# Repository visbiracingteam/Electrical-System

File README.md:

# Overview
### Contains all the files related to Electrical System of IITB-Racing

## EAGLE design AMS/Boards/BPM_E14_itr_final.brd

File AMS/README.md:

# AMS
### Contains all the files related to Accumulator Management System

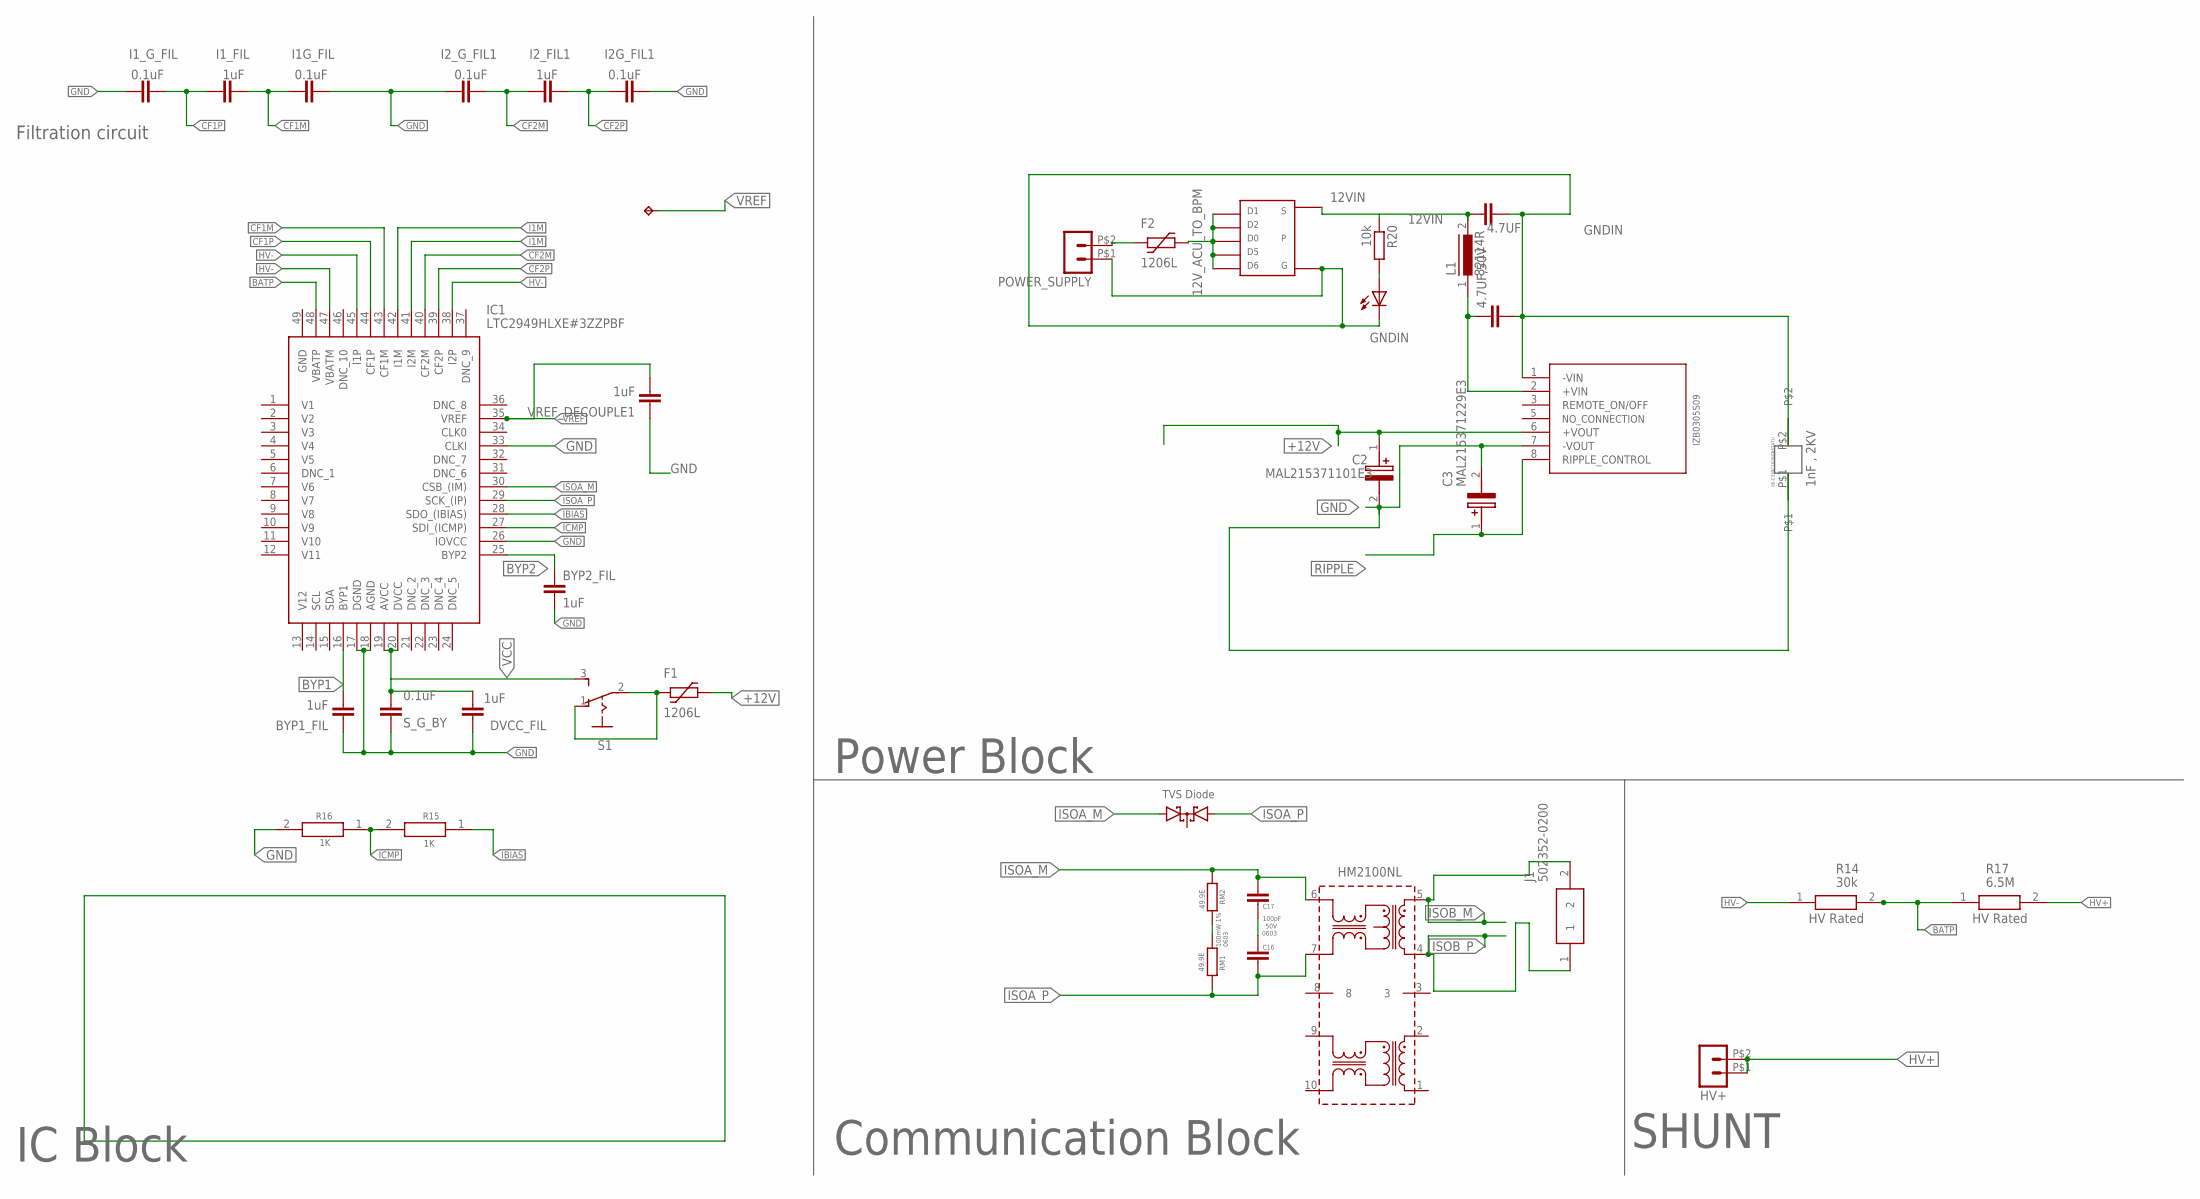
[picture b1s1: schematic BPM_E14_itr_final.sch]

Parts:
4.7UF, 4.7UF,50V: C-EUC1206; C1206
BYP1_FIL, BYP2_FIL: 1uF; C0603
C2: MAL215371101E3; CAPAE1060X1060N
C3: MAL215371229E3; CAPAE860X680N
C15: TPPAD1-13; P1-13
C16, C17: 100pF; C0603
DVCC_FIL: 1uF; C0603
F1, F2: 1206L
HM2100NL: HM2100NL
HV+: MOLEX2PIN43650-0200; 43650-0200
I1G_FIL, I1_G_FIL, I2G_FIL1, I2_G_FIL1: 0.1uF; C0603
I1_FIL, I2_FIL1: 1uF; C0603
IC1: LTC2949HLXE#3ZZPBF; QFP50P900X900X160-49N
IM1: TVS; SOT23
J1: 502352-0200; 5023520200
L1: 82114R
POWER_SUPPLY: MOLEX2PIN43045-0212; 43045-0212
PWR_LED: LED-FKIT-1206; FKIT-LED-1206
R14: 30k; RESC3216X70N
R15, R16: 1K; RESC1608X50N
R17: 6.5M; RESC3216X70N
R20: 10k; R0805
RM1, RM2: 49.9E; R0603
S1: STS121PC04
S_G_BY: 0.1uF; C0603
U$1: BPM_CONV
U$2: 80-C330C102KGR5TATU
U$10: TSOP-6_PMOS
VREF_DECOUPLE1: 1uF; C0603

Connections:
12VIN: 4.7UF.1, L1.2, R20.1, U$10.S
12V_ACU_TO_BPM: F2.P$2 (2), U$10.1, U$10.2, U$10.5, U$10.6, U$10.D (D0)
+12V: C2.1 (+), F1.P$2 (2), U$1.6 (+VOUT)
BATP: IC1.48 (VBATP), R14.2, R17.1
BYP1: BYP1_FIL.2, IC1.16 (BYP1)
BYP2: BYP2_FIL.1, IC1.25 (BYP2)
CF1M: I1G_FIL.1, I1_FIL.1, IC1.43 (CF1M)
CF1P: I1_FIL.2, I1_G_FIL.2, IC1.44 (CF1P)
CF2M: I2_FIL1.2, I2_G_FIL1.1, IC1.40 (CF2M)
CF2P: I2G_FIL1.1, I2_FIL1.1, IC1.39 (CF2P)
GND: BYP1_FIL.1, BYP2_FIL.2, C2.2 (-), C3.2 (-), DVCC_FIL.1, I1G_FIL.2, I1_G_FIL.1, I2G_FIL1.2, I2_G_FIL1.2, IC1.17 (DGND), IC1.18 (AGND), IC1.26 (IOVCC), IC1.33 (CLKI), R16.2, S_G_BY.1, U$1.7 (-VOUT), U$2.P$1, VREF_DECOUPLE1.1
GNDIN: 4.7UF.2, 4.7UF,50V.2, POWER_SUPPLY.P$1 (1), PWR_LED.C, U$1.1 (-VIN), U$2.P$2, U$10.G
HV+: HV+.P$1 (1), HV+.P$2 (2), R17.2
HV-: IC1.38 (I2P), IC1.45 (I1P), IC1.47 (VBATM), R14.1
I1M: IC1.41 (I2M), IC1.42 (I1M)
IBIAS: IC1.28 (SDO_(IBIAS)), R15.1
ICMP: IC1.27 (SDI_(ICMP)), R15.2, R16.1
ISOA_M: C17.2, HM2100NL.6, IC1.30 (CSB_(IM)), IM1.2 (A2), RM2.1
ISOA_P: C16.1, HM2100NL.7, IC1.29 (SCK_(IP)), IM1.1 (A1), RM1.2
ISOB_M: HM2100NL.5, J1.2
ISOB_P: HM2100NL.4, J1.1
N$: RM1.1, RM2.2
unnamed: 4.7UF,50V.1, L1.1, U$1.2 (+VIN)
unnamed: F2.P$1 (1), POWER_SUPPLY.P$2 (2)
unnamed: PWR_LED.A, R20.2
unnamed: F1.P$1 (1), S1.1 (O), S1.2
unnamed: C16.2, C17.1
RIPPLE: C3.1 (+), U$1.8 (RIPPLE_CONTROL)
VCC: DVCC_FIL.2, IC1.19 (AVCC), IC1.20 (DVCC), S1.3 (S), S_G_BY.2
VREF: C15.TP, IC1.35 (VREF), VREF_DECOUPLE1.2

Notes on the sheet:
50V 0603
100mW 1% 0603
TVS Diode
Communication Block
IC Block
SHUNT
Power Block
Filtration circuit
HV Rated

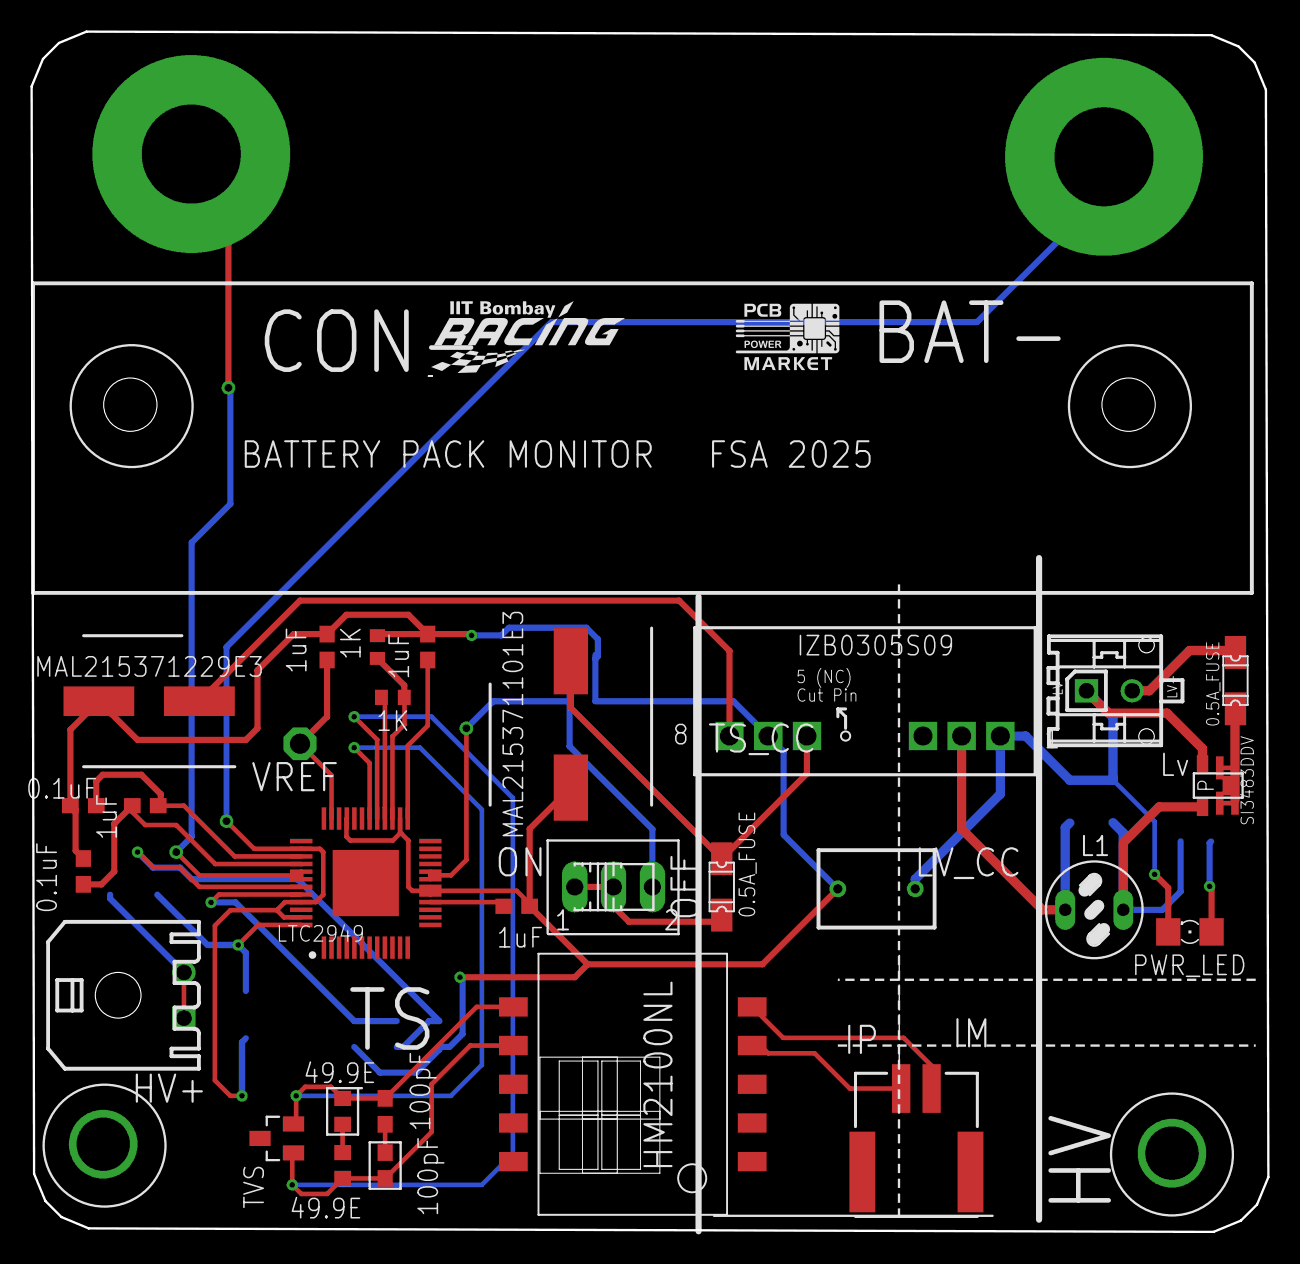
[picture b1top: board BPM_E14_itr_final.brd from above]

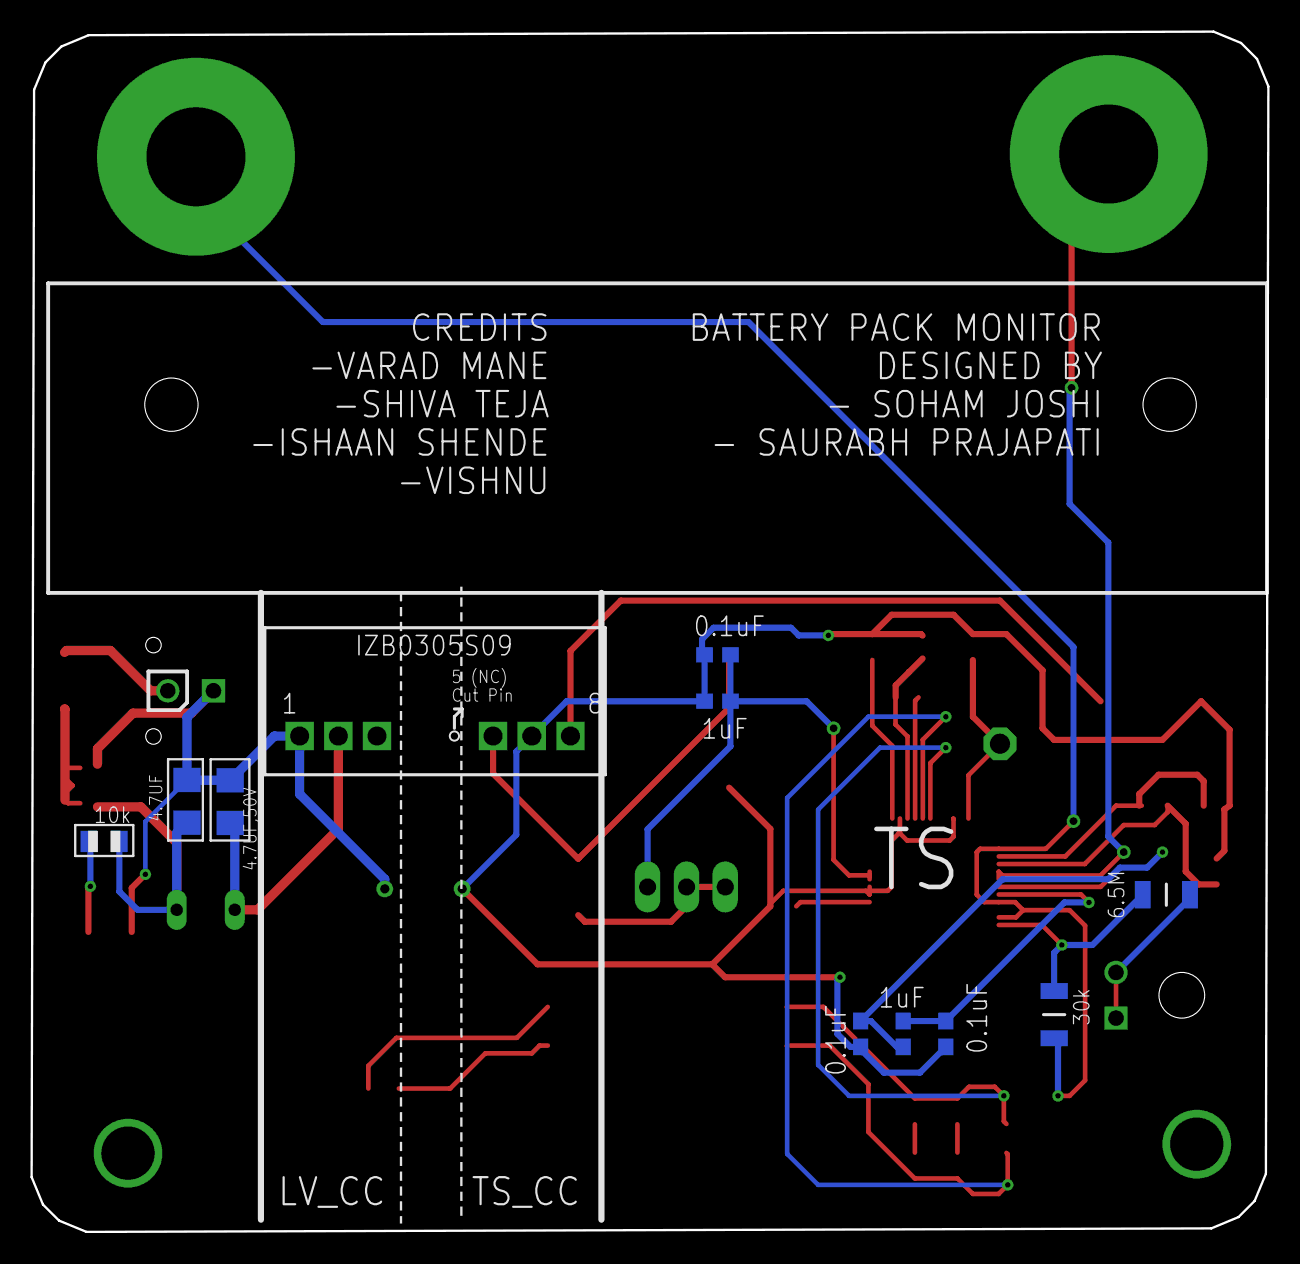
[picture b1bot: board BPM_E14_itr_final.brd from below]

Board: 2 copper layers, 81.2 x 78.8 mm, 41 parts (10 on the bottom side), 30 nets.

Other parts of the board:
U$6: LOGO_PCBPOWER; 270X170
U$22: RACING_LOGO_190MIL

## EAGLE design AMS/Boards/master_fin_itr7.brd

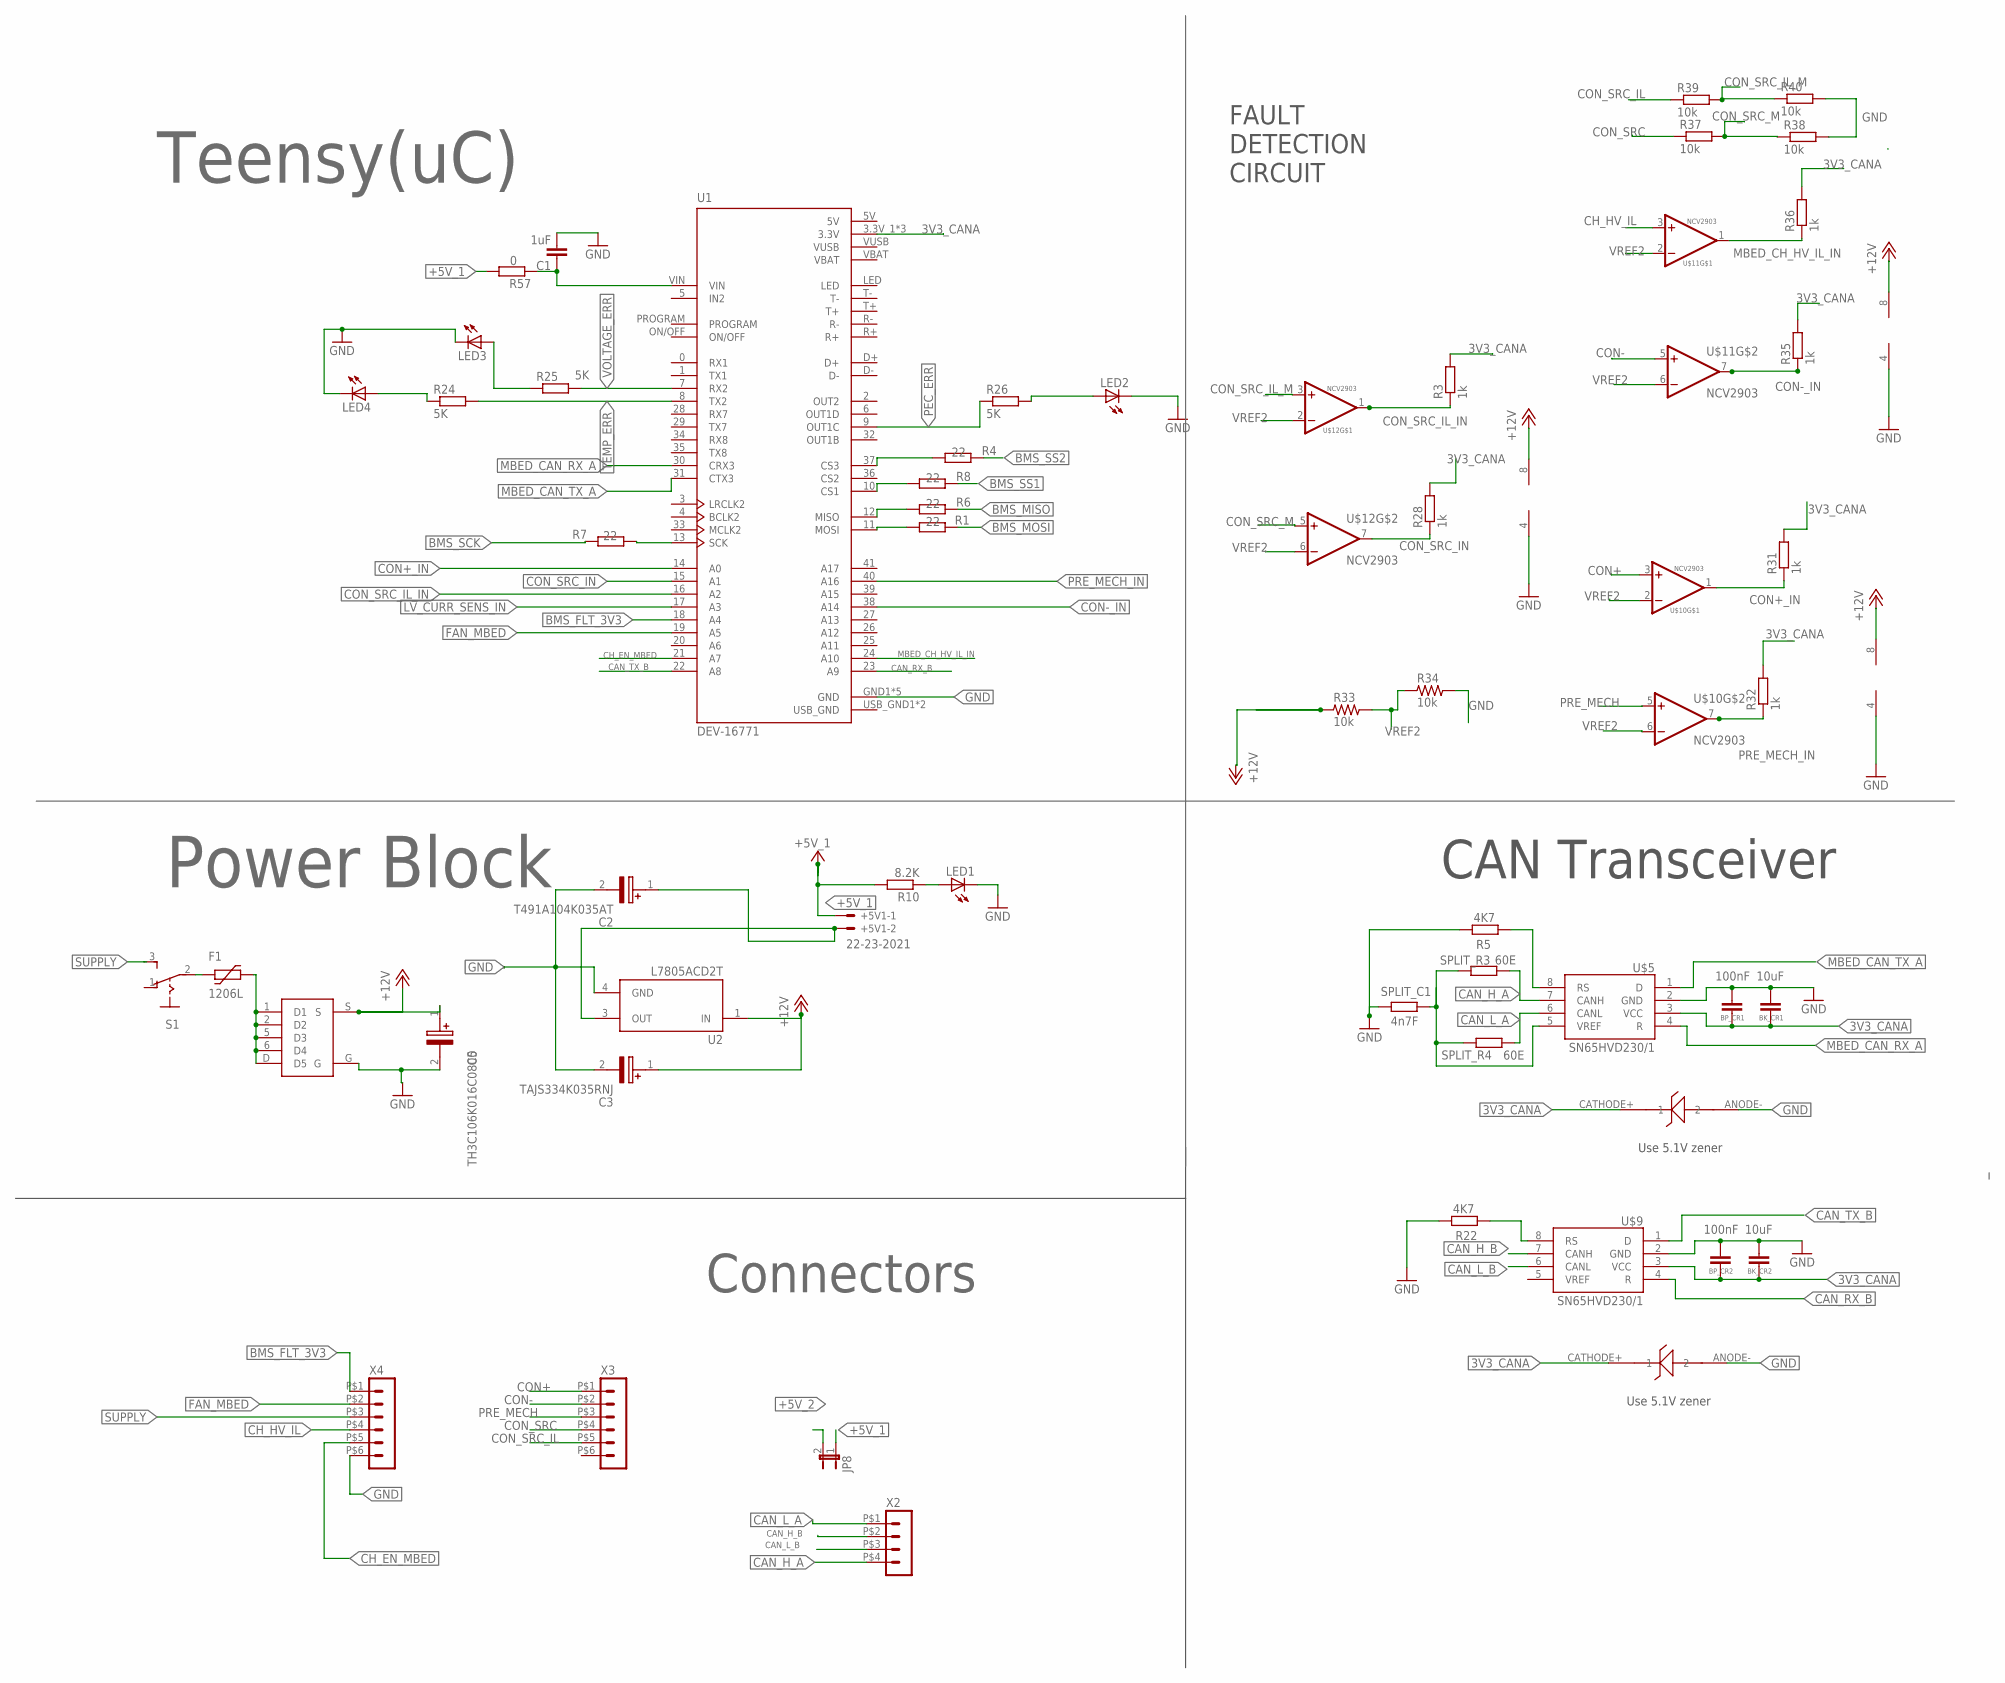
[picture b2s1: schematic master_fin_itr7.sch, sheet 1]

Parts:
+5V1: 22-23-2021
BK_CR1, BK_CR2: 10uF; C0805
BP_CR1, BP_CR2: 100nF; C0805
C1: 1uF; C0805K
C2: T491A104K035AT; T491A
C3: TAJS334K035RNJ; CAPPM3216X120N
C5: TH3C106K016C0800; CAPPM6032X280N
F1: 1206L
JP8: JP1E; JP1
LED1, LED2, LED3, LED4: LED; CHIP-LED0805
R1, R4, R6, R7, R8: 22; R0805
R3, R28, R31, R32, R35, R36: 1k; M0805
R5, R22: 4K7; R0805
R10: 8.2K; R0805
R24, R25, R26: 5K; R0805
R33, R34: 10k; RC-MASTER-SMD_R0603MP
R37, R38, R39, R40: 10k; M0805
R57: 0; R0805
S1: STS121PC04
S4: DMP3125L/SQ3419AEEV
SPLIT_C1: 4n7F; R0805
SPLIT_R3, SPLIT_R4: 60E; R0805
U1: DEV-16771; MODULE_DEV-16771
U2: L7805ACD2T; VREG_L7805ACD2T
U$5, U$9: SN65HVD230/1; SO8
U$6, U$8: ZENER_DIODE; SOD323HE
U$10, U$11, U$12: NCV2903; SOIC-8
X2: CON-MOLEX-MICRO-FIT-3_0_HEADER_POS4_43045-0412; CON-MOLEX-MICRO-FIT-3_0_43045-0412
X3, X4: HEADER_POS6_43045-0612; 43045-0612

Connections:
3V3_CANA: BK_CR1.1, BK_CR2.1, BP_CR1.1, BP_CR2.1, R3.2, R28.2, R31.2, R32.2, R35.2, R36.2, U1.3.3V_1 (3.3V), U1.3.3V_2 (3.3V), U1.3.3V_3 (3.3V), U$5.3 (VCC), U$6.CATHODE+ (1), U$8.CATHODE+ (1), U$9.3 (VCC)
5V: U1.5V
+5V_1: +5V1.1, JP8.1, R10.2, R57.2
+5V_2: JP8.2; also elsewhere on the board
+12V: C3.1 (+), C5.1 (+), R33.1, S4.S, U2.1 (IN), U$10.8 (V+), U$11.8 (V+), U$12.8 (V+)
BMS_FLT_3V3: U1.18 (A4), X4.P$1 (1)
BMS_MISO: R6.1; also elsewhere on the board
BMS_MOSI: R1.1; also elsewhere on the board
BMS_SCK: R7.1; also elsewhere on the board
BMS_SS1: R8.1; also elsewhere on the board
BMS_SS2: R4.1; also elsewhere on the board
CAN_H_A: SPLIT_R3.1, U$5.7 (CANH), X2.P$4 (4)
CAN_H_B: U$9.7 (CANH), X2.P$2 (2)
CAN_L_A: SPLIT_R4.1, U$5.6 (CANL), X2.P$1 (1)
CAN_L_B: U$9.6 (CANL), X2.P$3 (3)
CAN_RX_B: U1.23 (A9), U$9.4 (R)
CAN_TX_B: U1.22 (A8), U$9.1 (D)
CH_EN_MBED: U1.21 (A7), X4.P$5 (5)
CH_HV_IL: U$11.3 (+IN), X4.P$4 (4)
CON+: U$10.3 (+IN), X3.P$1 (1)
CON+_IN: R31.1, U1.14 (A0), U$10.1 (OUT)
CON-: U$11.5 (+IN), X3.P$2 (2)
CON-_IN: R35.1, U1.38 (A14), U$11.7 (OUT)
CON_SRC: R37.1, X3.P$4 (4)
CON_SRC_IL: R39.1, X3.P$5 (5)
CON_SRC_IL_IN: R3.1, U1.16 (A2), U$12.1 (OUT)
CON_SRC_IL_M: R39.2, R40.1, U$12.3 (+IN)
CON_SRC_IN: R28.1, U1.15 (A1), U$12.7 (OUT)
CON_SRC_M: R37.2, R38.1, U$12.5 (+IN)
FAN_MBED: U1.19 (A5), X4.P$2 (2)
GND: BK_CR1.2, BK_CR2.2, BP_CR1.2, BP_CR2.2, C1.2, C2.2 (-), C3.2 (-), C5.2 (-), LED1.C, LED2.C, LED3.C, LED4.C, R5.1, R22.1, R34.2, R38.2, R40.2, S4.G, SPLIT_C1.2, U1.GND1 (GND), U1.GND2 (GND), U1.GND3 (GND), U1.GND4 (GND), U1.GND5 (GND), U2.4 (GND), U$5.2 (GND), U$6.ANODE- (2), U$8.ANODE- (2), U$9.2 (GND), U$10.4 (V-), U$11.4 (V-), U$12.4 (V-), X4.P$6 (6); also elsewhere on the board
LV_CURR_SENS_IN: U1.17 (A3)
MBED_CAN_RX_A: U1.30 (CRX3), U$5.4 (R)
MBED_CAN_TX_A: U1.31 (CTX3), U$5.1 (D)
MBED_CH_HV_IL_IN: R36.1, U1.24 (A10), U$11.1 (OUT)
unnamed: R4.2, U1.37 (CS3)
unnamed: F1.P$1 (1), S1.2
unnamed: R5.2, U$5.8 (RS)
unnamed: R22.2, U$9.8 (RS)
unnamed: R1.2, U1.11 (MOSI)
unnamed: R6.2, U1.12 (MISO)
unnamed: R8.2, U1.10 (CS1)
unnamed: R7.2, U1.13 (SCK)
unnamed: +5V1.2, C2.1 (+), U2.3 (OUT)
unnamed: LED1.A, R10.1
unnamed: LED3.A, R25.1
unnamed: LED4.A, R24.1
unnamed: LED2.A, R26.2
unnamed: SPLIT_C1.1, SPLIT_R3.2, SPLIT_R4.2, U$5.5 (VREF)
unnamed: F1.P$2 (2), S4.1 (D1), S4.2 (D2), S4.5 (D3), S4.6 (D4), S4.D (D5)
unnamed: C1.1, R57.1, U1.VIN
PEC_ERR: R26.1, U1.9 (OUT1C)
PRE_MECH: U$10.5 (+IN), X3.P$3 (3)
PRE_MECH_IN: R32.1, U1.40 (A16), U$10.7 (OUT)
SUPPLY: S1.3 (S), X4.P$3 (3)
TEMP_ERR: R24.2, U1.8 (TX2)
USB_GND: U1.USB_GND1 (USB_GND), U1.USB_GND2 (USB_GND)
VOLTAGE_ERR: R25.2, U1.7 (RX2)
VREF2: R33.2, R34.1, U$10.2 (-IN), U$10.6 (-IN), U$11.2 (-IN), U$11.6 (-IN), U$12.2 (-IN), U$12.6 (-IN)

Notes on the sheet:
CAN Transceiver
Power Block
Use 5.1V zener
Connectors
Teensy(uC)
FAULT DETECTION CIRCUIT

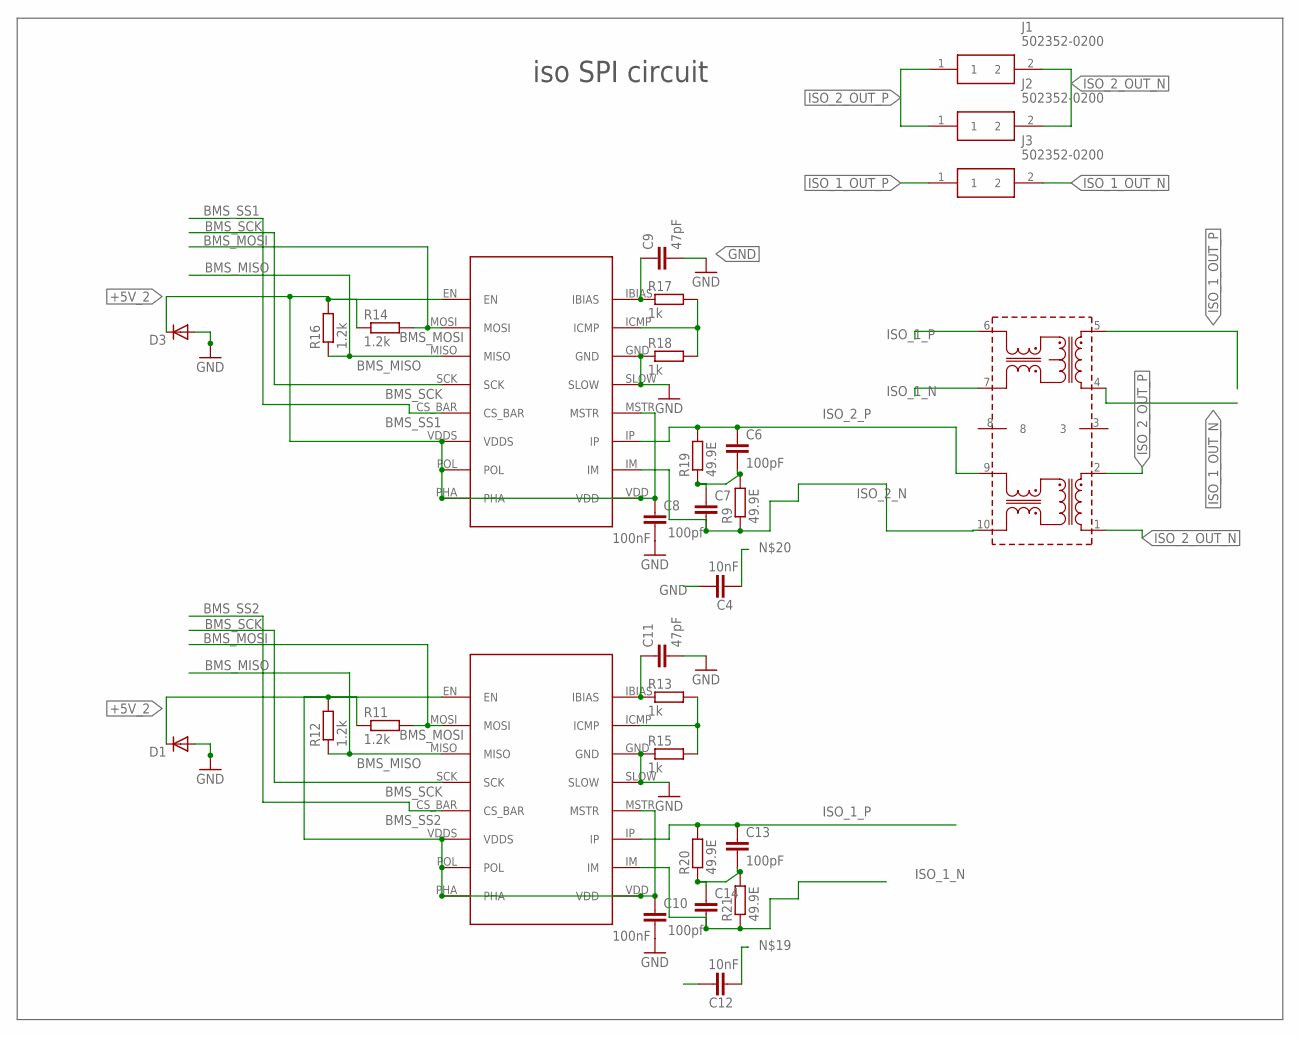
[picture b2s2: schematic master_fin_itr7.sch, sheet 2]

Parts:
C4, C12: 10nF; C0805
C6, C13: 100pF; C0603
C7, C14: 100pf; C0603
C8, C10: 100nF; C0805
C9, C11: 47pF; C0805
D1, D3: DIODE-SOD123; SOD123
J1, J2, J3: 502352-0200; 5023520200
R9, R19, R20, R21: 49.9E; R0805
R11, R12, R14, R16: 1.2k; R0805
R13, R15, R17, R18: 1k; R0805
U$1, U$4: LTC6820; 16-PINMSOP
U$2: HM2100NL

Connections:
+5V_2: C8.1, C10.1, D1.C, D3.C, R11.1, R12.2, R14.1, R16.2, U$1.EN, U$1.MSTR, U$1.PHA, U$1.POL, U$1.VDD, U$1.VDDS, U$4.EN, U$4.MSTR, U$4.PHA, U$4.POL, U$4.VDD, U$4.VDDS; also elsewhere on the board
BMS_MISO: R12.1, R16.1, U$1.MISO, U$4.MISO; also elsewhere on the board
BMS_MOSI: R11.2, R14.2, U$1.MOSI, U$4.MOSI; also elsewhere on the board
BMS_SCK: U$1.SCK, U$4.SCK; also elsewhere on the board
BMS_SS1: U$1.CS_BAR; also elsewhere on the board
BMS_SS2: U$4.CS_BAR; also elsewhere on the board
GND: C4.1, C8.2, C9.2, C10.2, C11.2, C12.1, D1.A, D3.A, R15.1, R18.1, U$1.GND, U$1.SLOW, U$4.GND, U$4.SLOW; also elsewhere on the board
ISO_1_N: C14.2, R21.1, U$2.7, U$4.IM
ISO_1_OUT_N: J3.2, U$2.4
ISO_1_OUT_P: J3.1, U$2.5
ISO_1_P: C13.1, R20.2, U$2.6, U$4.IP
ISO_2_N: C7.2, R9.1, U$1.IM, U$2.10
ISO_2_OUT_N: J1.2, J2.2, U$2.1
ISO_2_OUT_P: J1.1, J2.1, U$2.2
ISO_2_P: C6.1, R19.2, U$1.IP, U$2.9
unnamed: R17.2, R18.2, U$1.ICMP
unnamed: C9.1, R17.1, U$1.IBIAS
unnamed: R13.2, R15.2, U$4.ICMP
unnamed: C11.1, R13.1, U$4.IBIAS
unnamed: C12.2, C13.2, C14.1, R20.1, R21.2
unnamed: C4.2, C6.2, C7.1, R9.2, R19.1

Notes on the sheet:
iso SPI circuit

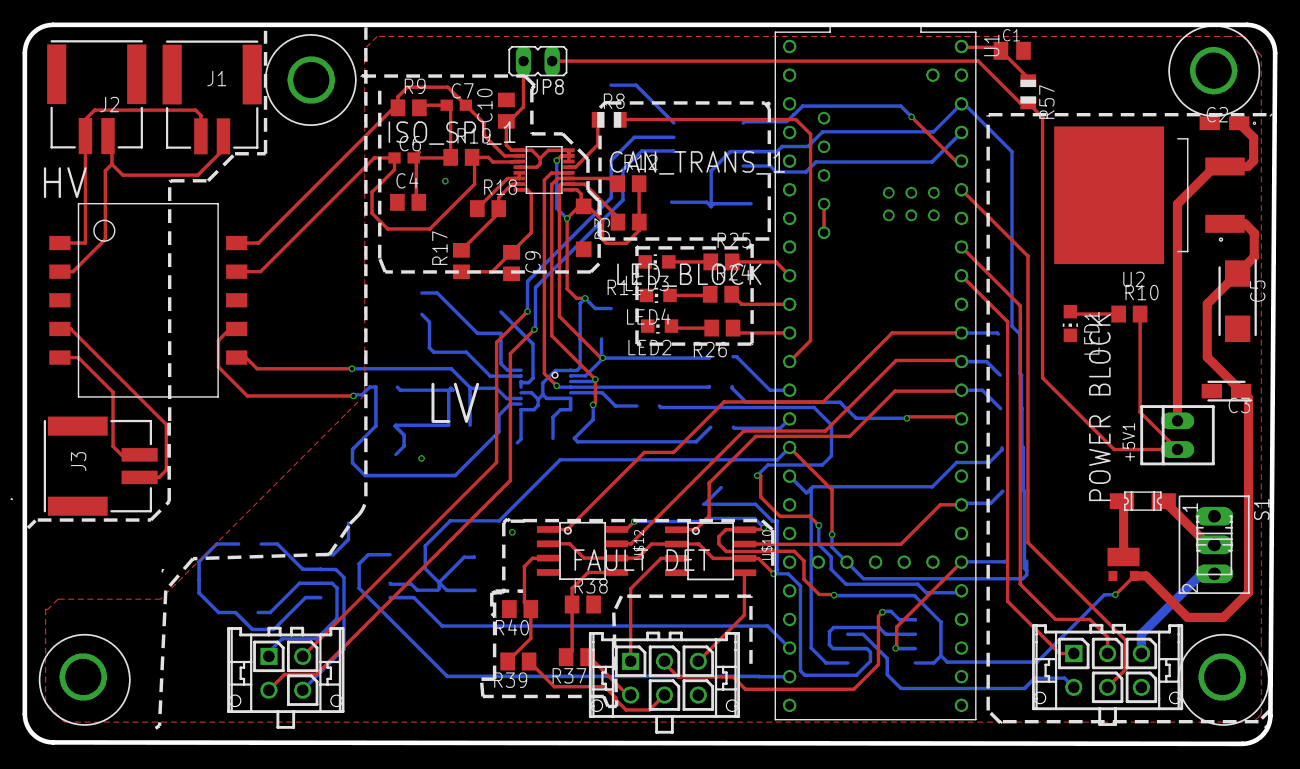
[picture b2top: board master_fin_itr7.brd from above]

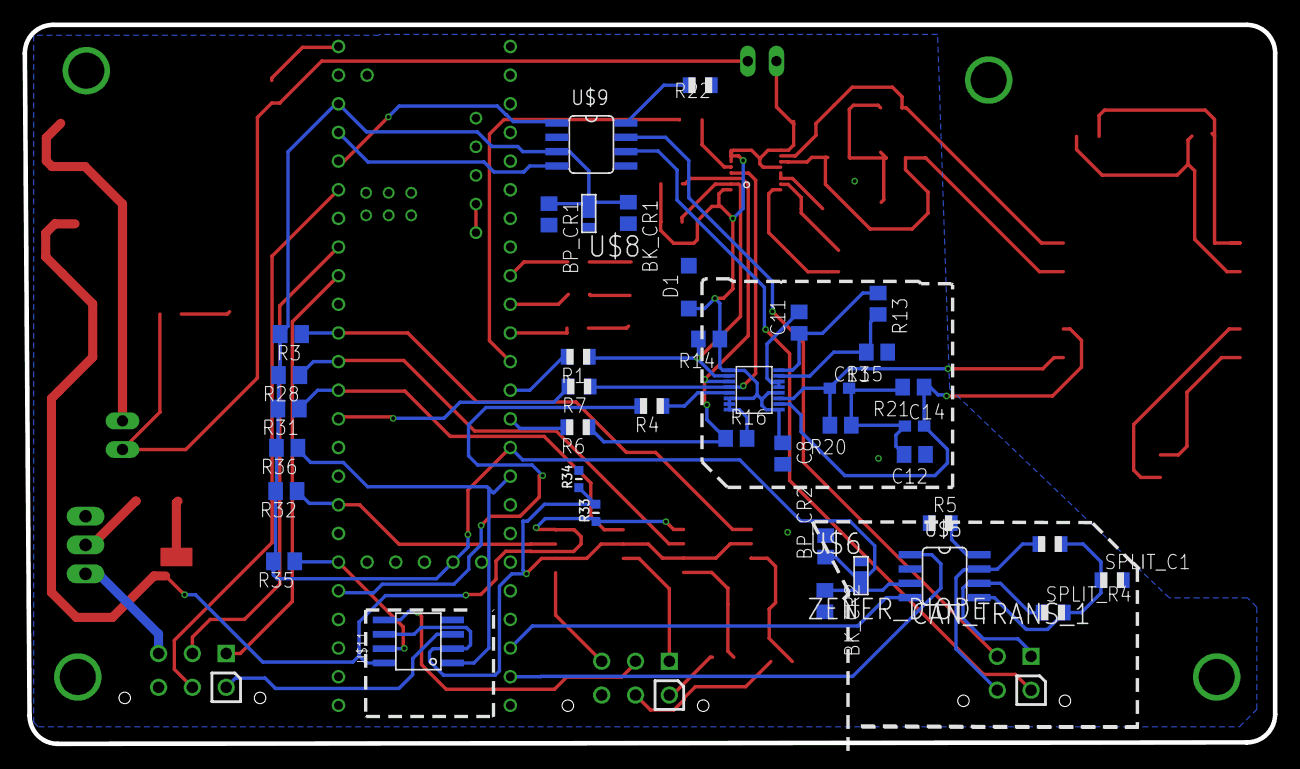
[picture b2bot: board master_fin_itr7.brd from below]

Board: 2 copper layers, 110.9 x 63.8 mm, 86 parts (39 on the bottom side), 71 nets.

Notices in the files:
parts and their libraries:
SparkFun-Aesthetics: Licensing: Creative Commons ShareAlike 4.0 International - https://creativecommons.org/licenses/by-sa/4.0
SparkFun-Aesthetics: Licensing: CC v3.0 Share-Alike You are welcome to use this library for commercial purposes.
